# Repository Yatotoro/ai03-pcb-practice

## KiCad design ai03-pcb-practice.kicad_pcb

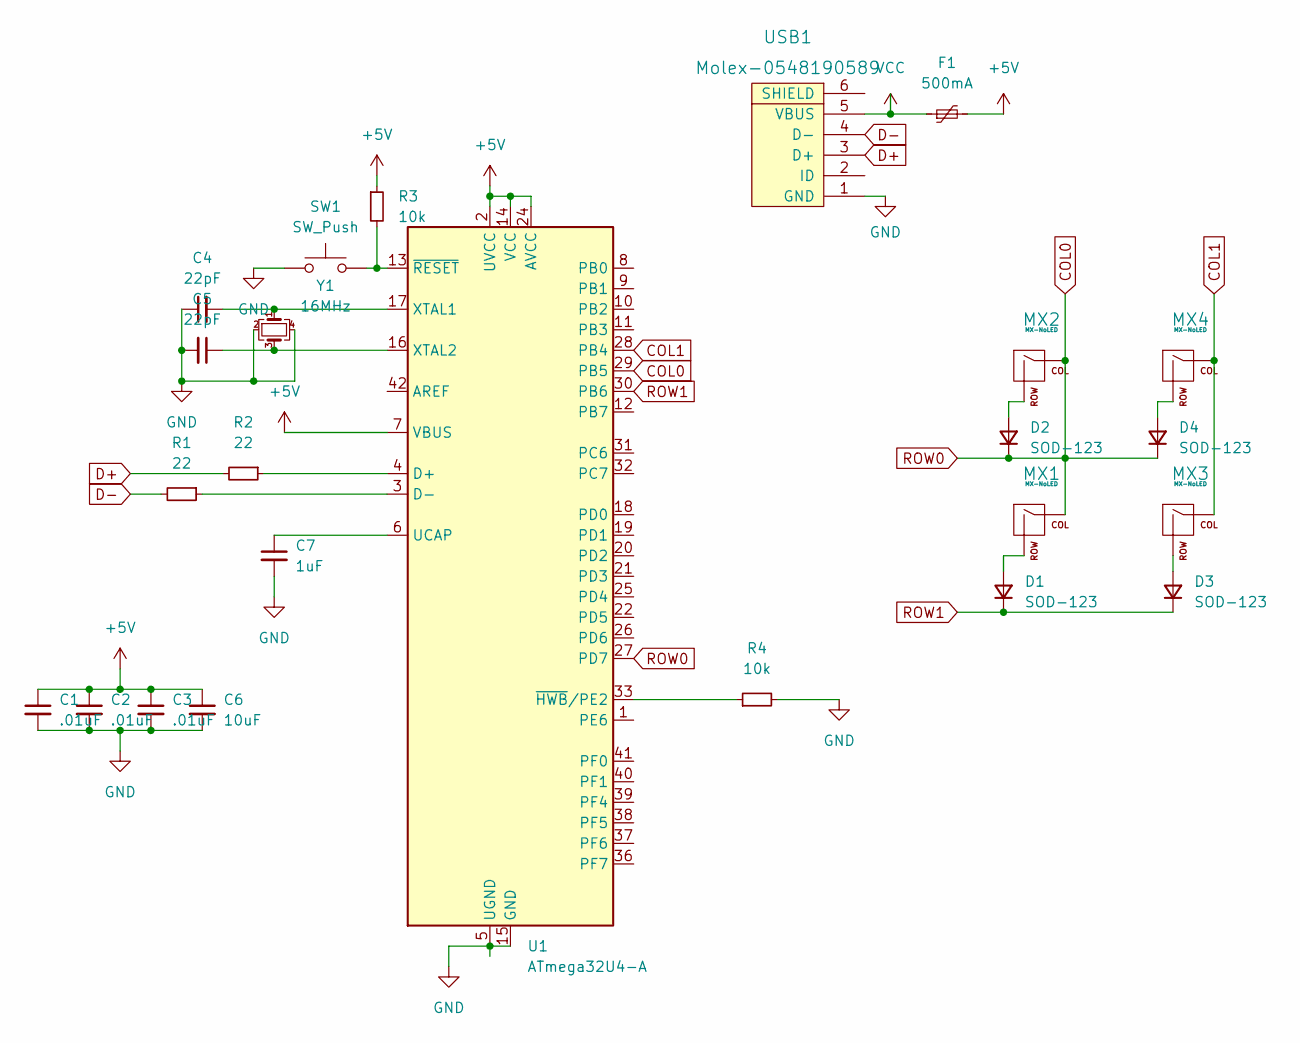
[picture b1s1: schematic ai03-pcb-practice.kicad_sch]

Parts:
C1, C2, C3: .01uF; C_0805_2012Metric
C4, C5: 22pF; C_0805_2012Metric
C6: 10uF; C_0805_2012Metric
C7: 1uF; C_0805_2012Metric
D1, D2, D3, D4: SOD-123; D_SOD-123
F1: 500mA; Fuse_1206_3216Metric
MX1, MX2, MX3, MX4: MX-NoLED; MX-1U-NoLED
R1, R2: 22; R_0805_2012Metric
R3, R4: 10k; R_0805_2012Metric
SW1: SW_Push; SKQG-1155865
U1: ATmega32U4-A; TQFP-44_10x10mm_P0.8mm
USB1: Molex-0548190589
Y1: 16MHz; Crystal_SMD_3225-4Pin_3.2x2.5mm

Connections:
+5V: C1.1, C2.1, C3.1, C6.1, F1.2, R3.1, U1.2 (UVCC), U1.7 (VBUS), U1.14 (VCC), U1.24 (AVCC), U1.34 (VCC), U1.44 (AVCC)
COL0: D2.1 (K), D4.1 (K), MX1.1 (COL), MX2.1 (COL), U1.27 (PD7), U1.29 (PB5)
COL1: MX3.1 (COL), MX4.1 (COL), U1.28 (PB4)
D+: R2.2, USB1.3 (D+)
D-: R1.2, USB1.4 (D-)
GND: C1.2, C2.2, C3.2, C4.1, C5.2, C6.2, C7.2, R4.2, SW1.1, U1.5 (UGND), U1.15 (GND), U1.23 (GND), U1.35 (GND), U1.43 (GND), USB1.1 (GND), Y1.2, Y1.4
unnamed: C4.2, U1.17 (XTAL1), Y1.1
unnamed: C5.1, U1.16 (XTAL2), Y1.3
unnamed: C7.1, U1.6 (UCAP)
unnamed: D1.2 (A), MX1.2 (ROW)
unnamed: D2.2 (A), MX2.2 (ROW)
unnamed: D3.2 (A), MX3.2 (ROW)
unnamed: D4.2 (A), MX4.2 (ROW)
unnamed: R1.1, U1.3 (D-)
unnamed: R2.1, U1.4 (D+)
unnamed: R3.2, SW1.2, U1.13 (~RESET)
unnamed: R4.1, U1.33 (~HWB/PE2)
ROW1: D1.1 (K), D3.1 (K), U1.30 (PB6)
VCC: F1.1, USB1.5 (VBUS)

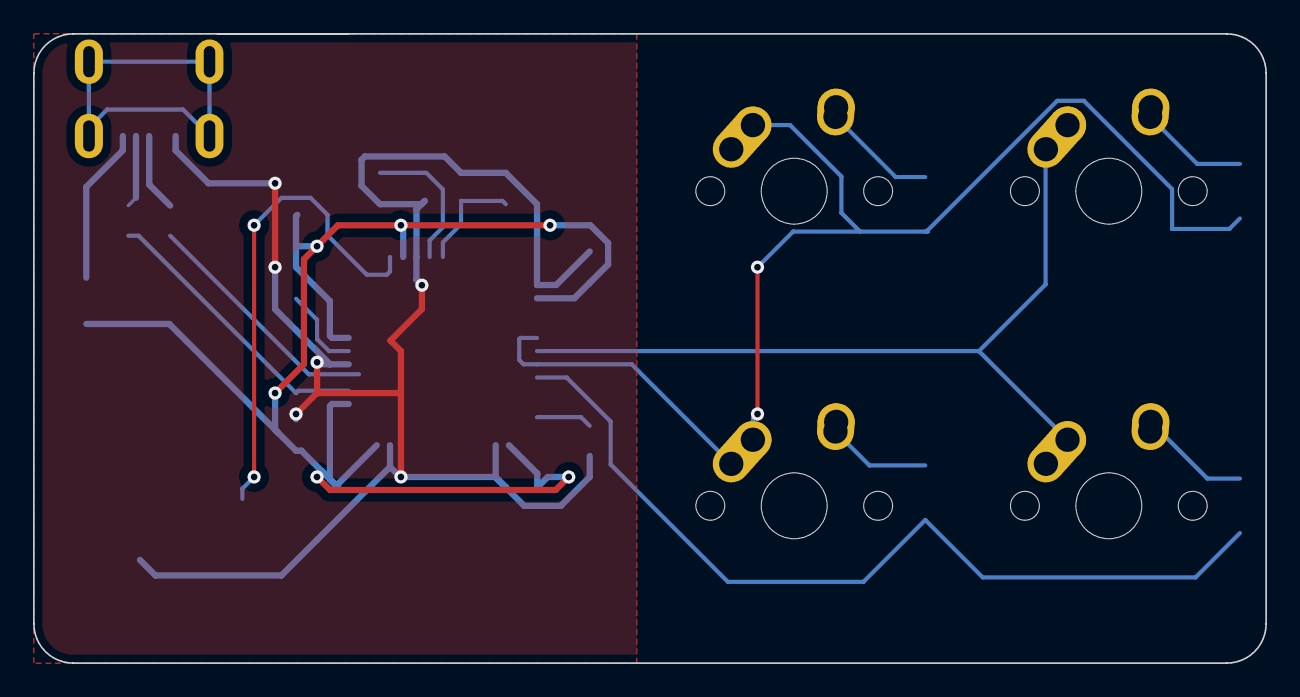
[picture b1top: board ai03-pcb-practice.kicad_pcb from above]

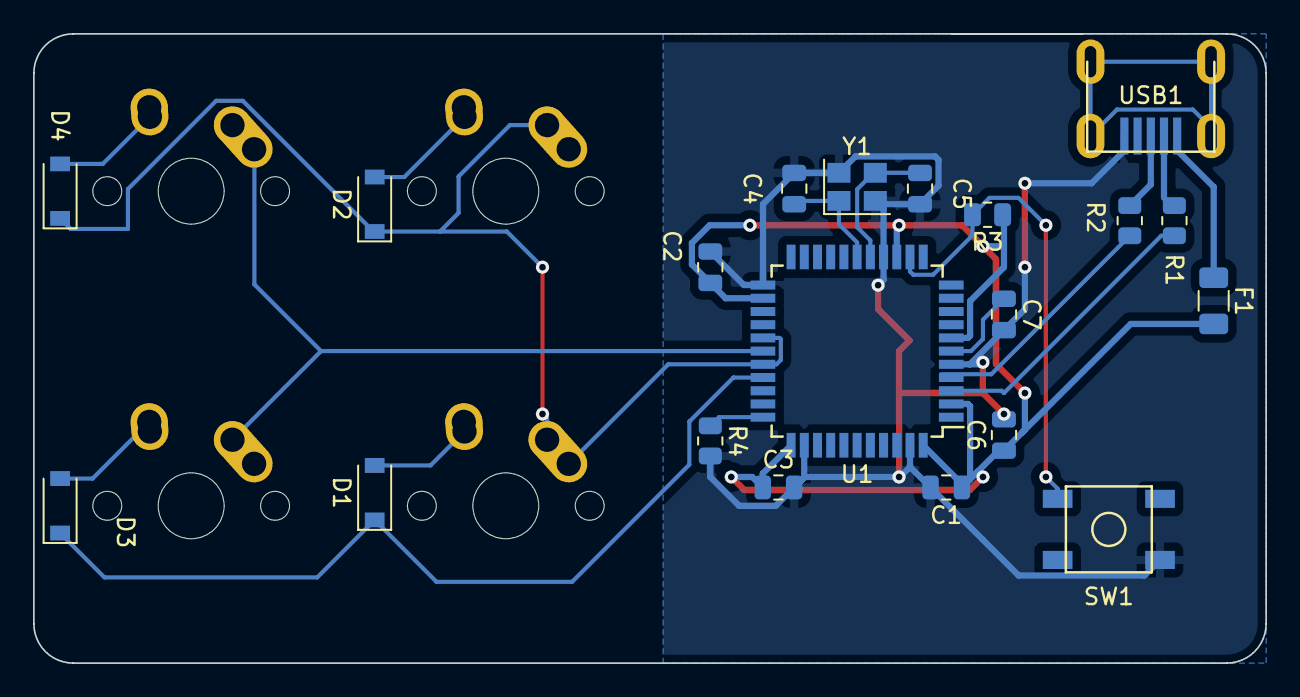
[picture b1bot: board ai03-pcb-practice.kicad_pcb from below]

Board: 2 copper layers, 74.6 x 38.1 mm, 24 parts (20 on the bottom side), 19 nets.

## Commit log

2022-09-10 Start
2022-09-10 Submodules
2022-09-10 Add footprint libraries
2022-09-10 Schematic
2022-09-10 Progress
2022-09-10 Fixing Errors
